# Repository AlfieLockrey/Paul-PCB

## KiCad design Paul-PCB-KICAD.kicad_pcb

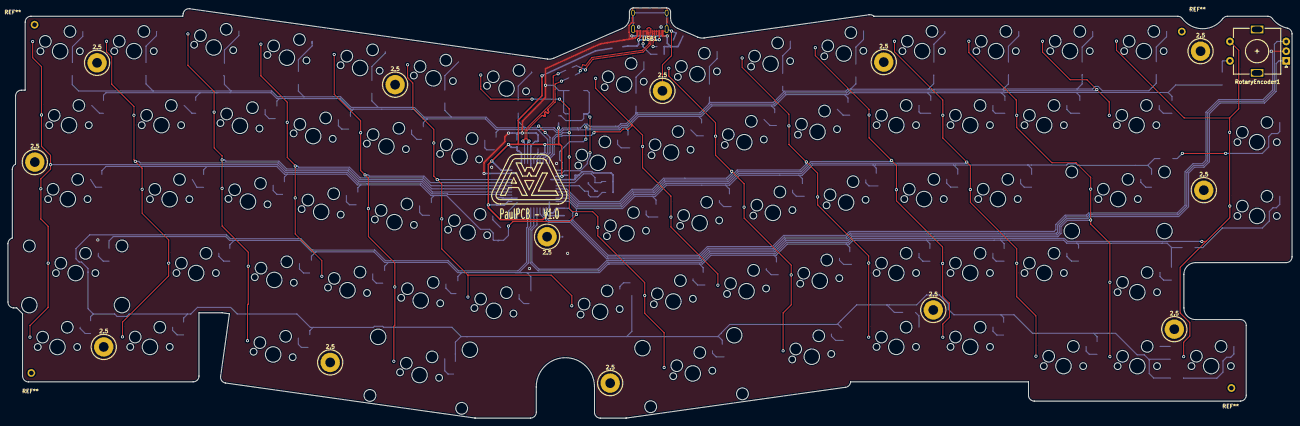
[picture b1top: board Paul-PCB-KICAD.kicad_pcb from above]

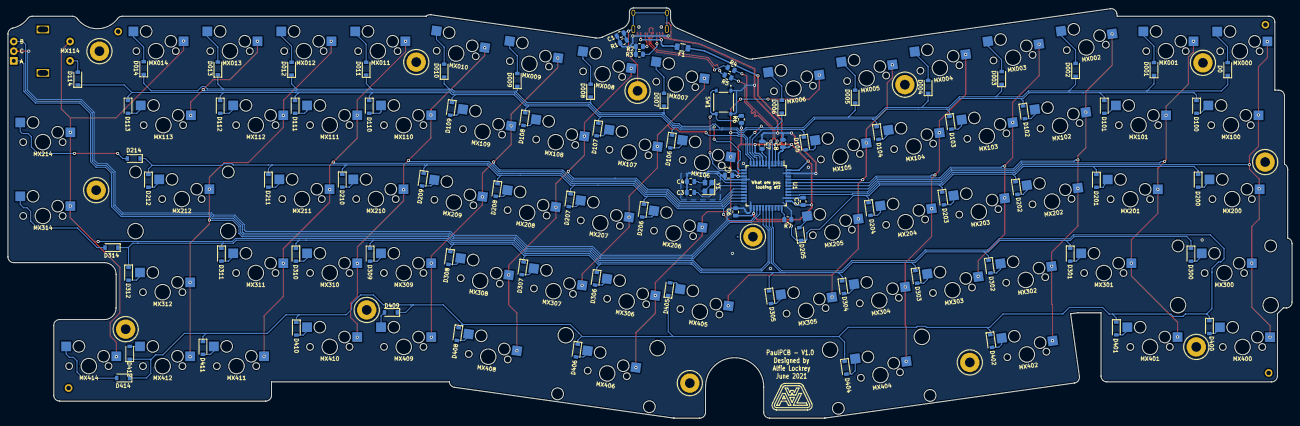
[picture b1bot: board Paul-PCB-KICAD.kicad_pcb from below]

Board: 2 copper layers, 330.9 x 105.7 mm, 173 parts (89 on the bottom side), 107 nets.

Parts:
2.5, 2.5#2, 2.5#3, 2.5#4, 2.5#5, 2.5#6, 2.5#7, 2.5#8, 2.5#9, 2.5#10, 2.5#11, 2.5#12, 2.5#13: 2.5_Mount; MountingHole_2.5mm_Pad
C1: 4.7nF; C_0805_2012Metric
C2, C5, C6: 0.1uF; C_0805_2012Metric
C3, C4: 22pF; C_0805_2012Metric
C7: 1uF; C_0805_2012Metric
C8: 10uF; C_0805_2012Metric
D0, D001, D002, D003, D004, D005, D006, D007, D008, D009, D010, D011, D012, D013, D014, D100, D101, D102, D103, D104, D105, D106, D107, D108, D109, D110, D111, D112, D113, D114, D200, D201, D202, D203, D204, D205, D206, D207, D208, D209, D210, D211, D212, D214, D300, D301, D302, D303, D304, D305, D306, D307, D308, D309, D310, D311, D312, D314, D400, D401, D402, D404, D405, D406, D408, D409, D410, D411, D412, D414: D_Small; D_SOD-123
F1: 500mA; Fuse_1206_3216Metric
MX000, MX001, MX002, MX003, MX004, MX005, MX006, MX007, MX008, MX009, MX010, MX011, MX012, MX013, MX014, MX101, MX102, MX103, MX104, MX105, MX106, MX107, MX108, MX109, MX110, MX111, MX112, MX201, MX202, MX203, MX204, MX205, MX206, MX207, MX208, MX209, MX210, MX211, MX214, MX301, MX302, MX303, MX304, MX305, MX306, MX307, MX308, MX309, MX310, MX311, MX312, MX314, MX405, MX408, MX409, MX410, MX411, MX412, MX414: MX-NoLED; MXOnly-1U-Hotswap
MX100, MX113: MX-NoLED; MXOnly-1.5U-Hotswap
MX200: MX-NoLED; MXOnly-1.75U-Hotswap
MX212, MX300: MX-NoLED; MXOnly-2.25U-Hotswap
MX400, MX401, MX402: MX-NoLED; MXOnly-1.25U-Hotswap
MX404: MX-NoLED; MXOnly-2.75U-Hotswap-ReversedStabilizers
MX406: MX-NoLED; MXOnly-2.25U-Hotswap-ReversedStabilizers
R1: 1M; R_0805_2012Metric
R2, R3: 5.1k; R_0805_2012Metric
R4, R5: 22; R_0805_2012Metric
R6, R7: 10k; R_0805_2012Metric
RotaryEncoder1: Rotary_Encoder_Switch; RotaryEncoder_Alps_EC11E-Switch_Vertical_H20mm
SW1: SW_Push; SW_TS-1187A-B-A-B
U1: ATmega32U4-AU; TQFP-44_10x10mm_P0.8mm
USB1: HRO-TYPE-C-31-M-12
Y1: 16MHz; Crystal_SMD_3225-4Pin_3.2x2.5mm

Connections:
+5V: C2.1, C5.1, C6.1, C8.1, F1.1, R6.1, U1.2, U1.7, U1.14, U1.24, U1.34, U1.44
/Data_N: R4.1, U1.3
/Data_P: R5.1, U1.4
/Reset: R6.2, SW1.C, SW1.D, U1.13
COL0: MX000.1, MX100.1, MX200.1, MX300.1, MX400.1, U1.36
COL1: MX001.1, MX101.1, MX201.1, MX301.1, MX401.1, U1.37
COL2: MX002.1, MX102.1, MX202.1, MX302.1, MX402.1, U1.38
COL3: MX003.1, MX103.1, MX203.1, MX303.1, U1.39
COL4: MX004.1, MX104.1, MX204.1, MX304.1, MX404.1, U1.40
COL5: MX005.1, MX105.1, MX205.1, MX305.1, MX405.1, U1.41
COL6: MX006.1, MX106.1, MX206.1, MX306.1, MX406.1, U1.10
COL7: MX007.1, MX107.1, MX207.1, MX307.1, U1.11
COL8: MX008.1, MX108.1, MX208.1, MX308.1, MX408.1, U1.18
COL9: MX009.1, MX109.1, MX209.1, MX309.1, MX409.1, U1.19
COL10: MX010.1, MX110.1, MX210.1, MX310.1, MX410.1, U1.20
COL11: MX011.1, MX111.1, MX211.1, MX311.1, MX411.1, U1.21
COL12: MX012.1, MX112.1, MX212.1, MX312.1, MX412.1, U1.27
COL13: MX013.1, MX113.1, U1.12
COL14: MX014.1, MX214.1, MX314.1, MX414.1, RotaryEncoder1.S1, U1.28
D+: R5.2, USB1.6, USB1.8
D-: R4.2, USB1.5, USB1.7
GND: C1.1, C2.2, C3.2, C4.2, C5.2, C6.2, C7.1, C8.2, R1.1, R2.1, R3.1, R7.1, RotaryEncoder1.C, SW1.A, SW1.B, U1.5, U1.15, U1.23, U1.35, U1.43, USB1.1, USB1.12, Y1.2, Y1.4
unnamed: 2.5#5.1, C1.2, R1.2, USB1.13
unnamed: C3.1, U1.17, Y1.1
unnamed: C4.1, U1.16, Y1.3
unnamed: C7.2, U1.6
unnamed: D0.2, MX000.2
unnamed: D001.2, MX001.2
unnamed: D002.2, MX002.2
unnamed: D003.2, MX003.2
unnamed: D004.2, MX004.2
unnamed: D005.2, MX005.2
unnamed: D006.2, MX006.2
unnamed: D007.2, MX007.2
unnamed: D008.2, MX008.2
unnamed: D009.2, MX009.2
unnamed: D010.2, MX010.2
unnamed: D011.2, MX011.2
unnamed: D012.2, MX012.2
unnamed: D013.2, MX013.2
unnamed: D014.2, MX014.2
unnamed: D100.2, MX100.2
unnamed: D101.2, MX101.2
unnamed: D102.2, MX102.2
unnamed: D103.2, MX103.2
unnamed: D104.2, MX104.2
unnamed: D105.2, MX105.2
unnamed: D106.2, MX106.2
unnamed: D107.2, MX107.2
unnamed: D108.2, MX108.2
unnamed: D109.2, MX109.2
unnamed: D110.2, MX110.2
unnamed: D111.2, MX111.2
unnamed: D112.2, MX112.2
unnamed: D113.2, MX113.2
unnamed: D200.2, MX200.2
unnamed: D201.2, MX201.2
unnamed: D202.2, MX202.2
unnamed: D203.2, MX203.2
unnamed: D204.2, MX204.2
unnamed: D205.2, MX205.2
unnamed: D206.2, MX206.2
unnamed: D207.2, MX207.2
unnamed: D208.2, MX208.2
unnamed: D209.2, MX209.2
unnamed: D210.2, MX210.2
unnamed: D211.2, MX211.2
unnamed: D212.2, MX212.2
unnamed: D214.2, MX214.2
unnamed: D300.2, MX300.2
unnamed: D301.2, MX301.2
unnamed: D302.2, MX302.2
unnamed: D303.2, MX303.2
unnamed: D304.2, MX304.2
unnamed: D305.2, MX305.2
unnamed: D306.2, MX306.2
unnamed: D307.2, MX307.2
unnamed: D308.2, MX308.2
unnamed: D309.2, MX309.2
unnamed: D310.2, MX310.2
unnamed: D311.2, MX311.2
unnamed: D312.2, MX312.2
unnamed: D314.2, MX314.2
unnamed: D400.2, MX400.2
unnamed: D401.2, MX401.2
unnamed: D402.2, MX402.2
unnamed: D404.2, MX404.2
unnamed: D405.2, MX405.2
unnamed: D406.2, MX406.2
unnamed: D408.2, MX408.2
unnamed: D409.2, MX409.2
unnamed: D410.2, MX410.2
unnamed: D411.2, MX411.2
unnamed: D412.2, MX412.2
unnamed: D414.2, MX414.2
unnamed: R2.2, USB1.4
unnamed: R3.2, USB1.10
unnamed: R7.2, U1.33
ROW0: D0.1, D001.1, D002.1, D003.1, D004.1, D005.1, D006.1, D007.1, D008.1, D009.1, D010.1, D011.1, D012.1, D013.1, D014.1, U1.9
ROW1: D100.1, D101.1, D102.1, D103.1, D104.1, D105.1, D106.1, D107.1, D108.1, D109.1, D110.1, D111.1, D112.1, D113.1, D114.1, U1.8
ROW2: D200.1, D201.1, D202.1, D203.1, D204.1, D205.1, D206.1, D207.1, D208.1, D209.1, D210.1, D211.1, D212.1, D214.1, U1.22
ROW3: D300.1, D301.1, D302.1, D303.1, D304.1, D305.1, D306.1, D307.1, D308.1, D309.1, D310.1, D311.1, D312.1, D314.1, U1.29
ROW4: D400.1, D401.1, D402.1, D404.1, D405.1, D406.1, D408.1, D409.1, D410.1, D411.1, D412.1, D414.1, U1.30
Rot.Enc.2: D114.2, RotaryEncoder1.S2
Rot.Enc.A: RotaryEncoder1.B, U1.25
Rot.Enc.B: RotaryEncoder1.A, U1.26
VCC: F1.2, USB1.2, USB1.11

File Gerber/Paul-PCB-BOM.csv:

Comment,Designator,Footprint,LCSC
4.7nF,C1,Capacitor_SMD:C_0805_2012Metric,C53987
22pF,"C3,C4",Capacitor_SMD:C_0805_2012Metric,C1653
0.1uF,"C2,C5,C6",Capacitor_SMD:C_0805_2012Metric,C14663
1uF,C7,Capacitor_SMD:C_0805_2012Metric,C15849
10uF,C8,Capacitor_SMD:C_0805_2012Metric,C19702
D_Small,"D0,D1,D2,D3,D4,D5,D6,D7,D8,D9,D10,D11,D12,D13,D14,D100,D101,D102,D103,D104,D105,D106,D107,D108,D109,D110,D111,D112,D113,D114,D200,D201,D202,D203,D204,D205,D206,D207,D208,D209,D210,D211,D212,D214,D300,D301,D302,D303,D304,D305,D306,D307,D308,D309,D310,D311,D312,D314,D400,D401,D402,D404,D405,D406,D408,D409,D410,D411,D412,D414",Diode_SMD:D_SOD-123,C64898
500mA,F1,Fuse:Fuse_1206_3216Metric,C315893
1M,R1,Resistor_SMD:R_0805_2012Metric,C17514
5.1k,"R2,R3",Resistor_SMD:R_0805_2012Metric,C27834
22,"R4,R5",Resistor_SMD:R_0805_2012Metric,C17561
10k,"R6,R7",Resistor_SMD:R_0805_2012Metric,C17414
SW_Push,SW1,TS-1187A-B-A-B:SW_TS-1187A-B-A-B,C318884
ATmega32U4-AU,U1,Package_QFP:TQFP-44_10x10mm_P0.8mm,C44854
HRO-TYPE-C-31-M-12,USB1,Type-C:HRO-TYPE-C-31-M-12,C165948
16MHz,Y1,Crystal:Crystal_SMD_3225-4Pin_3.2x2.5mm,C13738

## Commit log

2021-04-17 Initial Project
2021-04-17 Add submodules
2021-04-17 Create fp-info-cache
2021-04-17 USB and MCU Setup
2021-04-17 Fixed +5V for USB
2021-04-18 Added License and fixed PolyFuse Value
2021-04-19 Added Switch Layout to Schematic
2021-04-19 Started Adding Footprints
2021-04-20 Added Type-C Library
2021-04-20 Updated USB to 4084 GCT
2021-04-21 Added New Type-C Library
2021-06-13 Added Near Final Edge Cut and Positioned Switch footprints
    Need to add the diodes and caps and some cleanup
2021-06-16 More PCB Completed
    Added Mounting Holes as pads
2021-06-18 Further Completion
2021-06-28 Finished Prelim Diode Placement
    Beginning to Route Tracks
2021-06-29 Finished V1.0
    I think it may be done
2021-06-29 Added Ground Fill and Changed Reset Switch
    Added Ground Fill and Changed Reset Switch
2021-06-29 Changed Title to dashes
2021-07-19 Firmware First Issue
2021-07-19 Merge of Final PCB V1 and Firmware
    Firmware was on laptop and PCB on Desktop
2021-07-19 Firmware V1.1
    Fixed Layout naming mismatch and updated ReadMe
